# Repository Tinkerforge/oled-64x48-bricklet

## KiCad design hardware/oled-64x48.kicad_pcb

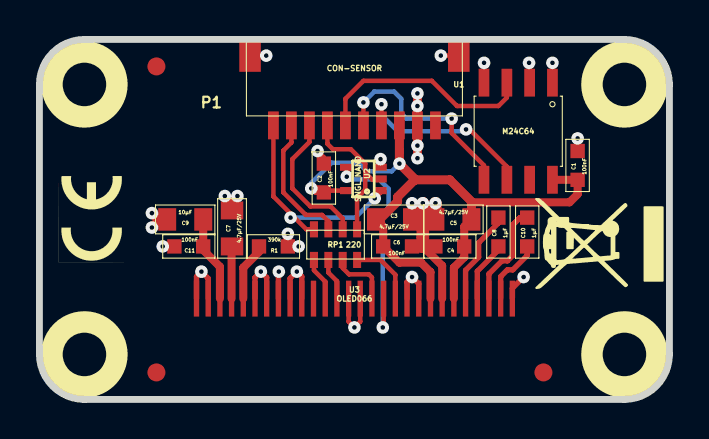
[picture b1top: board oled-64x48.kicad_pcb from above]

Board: 2 copper layers, 35.0 x 20.0 mm, 25 parts (0 on the bottom side), 21 nets.

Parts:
C1, C2, C4, C6, C11: 100nF; 0603
C3, C5, C7: 4.7µF/25V; 0805
C8, C10: 1µF; 0603
C9: 10µF; 0805
Fiducial_Mark: VAL**; Fiducial_Mark
Fiducial_Mark#2, Fiducial_Mark#3: VAL**; Fiducial_Mark
P1: CON-SENSOR
R1: 390k; 0603
RP1: 220; 0603X4
U1: M24C64; SOIC8
U2: SNGL_NAND; SC70-5
U3: OLED066
U4, U5, U6, U7: DRILL; DRILL_NP
VAL: CE_5mm

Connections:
3V3: C1.2, C2.2, C3.2, C4.2, C5.2, C6.2, P1.3, U1.8, U2.5, U3.6, U3.8
GND: C1.1, C2.1, C3.1, C4.1, C5.1, C6.1, C7.1, C9.1, C11.1, P1.2, P1.EP, R1.2, U1.1, U1.2, U1.4, U2.3, U3.1, U3.7, U3.9, U3.10, U3.14, U3.15, U3.19, U3.20, U3.21, U3.22, U3.23, U3.27, U3.28
unnamed: C7.2, U3.25
unnamed: C8.1, U3.5
unnamed: C8.2, U3.4
unnamed: C10.1, U3.3
unnamed: C10.2, U3.2
unnamed: C9.2, C11.2, U3.26
unnamed: P1.4, U1.6
unnamed: P1.5, U1.5
unnamed: P1.6, U1.3
unnamed: P1.7, RP1.1, U2.2
unnamed: P1.8, RP1.2
unnamed: P1.9, RP1.3
unnamed: P1.10, RP1.4, U2.1
unnamed: R1.1, U3.24
unnamed: RP1.5, U3.17
unnamed: RP1.6, U3.16
unnamed: RP1.7, U3.13
unnamed: RP1.8, U3.11
unnamed: U2.4, U3.12

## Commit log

2015-06-19 add first prototype of oled 64x48 Bricklet, partially routed
2015-06-21 first prototype finished
2015-06-22 Add Datasheets
2015-06-22 change module size and text
2015-06-25 add i2c pullup
2015-06-29 change to 4-wire SPI, add nand for reset control
2015-06-29 Add initial version of OLED software
2015-07-10 Add more defines, make sure to always set sdi low
2015-07-13 Add .gitignore
2015-07-23 Ignore eclipse related files
2015-07-23 Adding Python examples
2015-07-23 Adding C examples
2015-07-23 Adding C# examples
2015-07-23 Adding Java examples
2015-07-23 Adding JavaScript examples
2015-07-23 Adding Ruby examples
2015-07-23 Adding PHP examples
2015-07-26 Adding HelloWorld Delphi example
2015-07-26 Adding Delphi pixel matrix example
2015-07-26 Adding Shell hello world example
2015-07-27 Fix Delphi pixel matrix example
2015-07-27 Python3 specific changes
2015-07-27 Shell hello world example after test
2015-07-27 Remove unwanted print
2015-07-27 Cleanup C/C++, C#, Java, Python and Ruby examples
2015-07-27 VB.NET hello world example
2015-07-28 Cleanup whitespace and fix return type in C/C++ example
2015-07-29 Shell pixel matrix example
2015-07-29 Remove newline
2015-07-29 Adding Perl examples
2015-07-29 Reformat changelog
2015-07-29 Adding VB.NET pixel matrix example
2015-07-29 Use floor function and change UID to default for consistency
2015-07-29 Use floor function
2015-07-29 Adding MATLAB hello world example
2015-07-31 Adding MATLAB pixel matrix example
2015-07-31 Adding Octave hello world example
2015-07-31 Adding Octave pixel matrix example
2015-07-31 Calculate values from the constants
2015-08-03 Change UID for consistency
2015-08-03 Remove unused variable
2015-08-03 Minor fix
2015-08-03 Declare variable uniformly
2015-08-03 Consistent UID and minor changes
2015-08-03 Fix HTML example title
2015-08-03 Use constants
2015-08-03 Use constant
2015-08-03 Use constant and consistent UID
2015-08-03 Python 3 compatibility and use consistent UID
2015-08-03 Remove dot slash
2015-08-07 Use full device class name in Python examples
2015-08-12 Fix minor warnings in C/C++ examples
2015-08-14 Fix typo
2015-08-17 Cleanup Delphi examples
2015-08-18 Whitespace
2015-08-19 Cleanup Perl examples
2015-08-24 change pullup resistor to series resistor, fix routing
2015-09-09 Duplicate cmake call to fix bug during cmake creation
2015-09-17 add hardware version number
2015-10-20 drc check
2015-11-12 Generator based example cleanup
2015-11-12 matlab: Fix callback handling for R2014a
    http://undocumentedmatlab.com/blog/matlab-callbacks-for-java-events-in-r2014a
2015-11-25 Include date and commit into changelog
2016-01-05 Use better checkerboard pattern in examples
2016-01-05 Add Mathematica examples
2016-01-05 Add LabView examples
2016-01-05 python: Get image from command line
2016-01-06 vbnet: Fix strict type warning
2016-01-06 add schematic pdf
2016-01-07 Add font image generator
2016-01-07 Remove WIP marker
2016-01-11 Update changelog
2016-01-11 Add free-form drawing example for C#, Java and Python
2016-01-13 Add JavaScript (Node.js) example
2016-01-13 Some example logic cleanup
2016-01-14 Add VB.NET scribble example
2016-01-14 Add Perl scribble example
2016-01-14 Add PHP scribble example
2016-01-14 Add Ruby scribble example
2016-01-14 Add C scribble example
2016-01-28 vbnet: Use integer division
2016-02-08 Start extending examples to deal with different window sizes and positions
2016-02-08 perl: Fix warning
2016-02-09 vbnet: Fix compiler warning
2016-05-18 c: Add missing device destroy call
2016-07-01 Make the change UID comment more explicit
2017-06-02 octave: Use javaObject instead of deprecated java_new
2017-12-07 mathematica: Also generate .nb files
2018-02-19 javascript: Close div tag correctly
2018-02-20 Cleanup KiCad libraries config
    Ensure LibDir=kicad-libraries and LibName1=tinkerforge.
    Remove special library.
2018-05-24 perl: Use strict in examples
2018-07-11 Add Makefile with docker support
2018-07-11 Update directory structure and build instructions
2018-07-11 Remove obsolete generate_makefile scripts
2018-09-06 Add font preview image
2018-11-06 Add rust examples
2018-11-07 rust: Accept host names for ip connection, fix naming inconsistencies
2018-12-14 Add go examples.
2018-12-18 go: Change import path.
2018-12-18 go: Change import path again.
2018-12-20 rust: Reformat examples.
2019-01-24 mqtt: Add examples.
2019-01-24 mqtt: Fix example header.
2019-01-24 mqtt: Remove executable bit in example permissions.
2019-01-24 go: Minor example fixes.
2019-01-24 mqtt: Minor example fixes.
2019-08-13 Add updated font editor
2020-01-13 examples: Use python3 input instead of python2 raw_input.
2020-01-13 examples: mqtt: Remove trailing whitespace.
2020-01-14 examples: Use python3 input by default.
2020-02-26 examples: Update "Change UID" comment style
2020-03-18 rust: Update to new skeleton
2020-04-07 examples: rust: Always block when calling bindings functions.
2021-10-25 Update KiCad link
    https://www.kicad.org/blog/2021/10/Avoid-links-to-former-kicad-domain/
2022-03-07 Add code page 437 hint
2022-07-06 Add license files.
2024-02-23 vbnet: Fix for loops

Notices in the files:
hardware/oled-64x48.kicad_pcb:
Licensed under CERN OHL v.1.1
Copyright (©) 2015, B.Nordmeyer
